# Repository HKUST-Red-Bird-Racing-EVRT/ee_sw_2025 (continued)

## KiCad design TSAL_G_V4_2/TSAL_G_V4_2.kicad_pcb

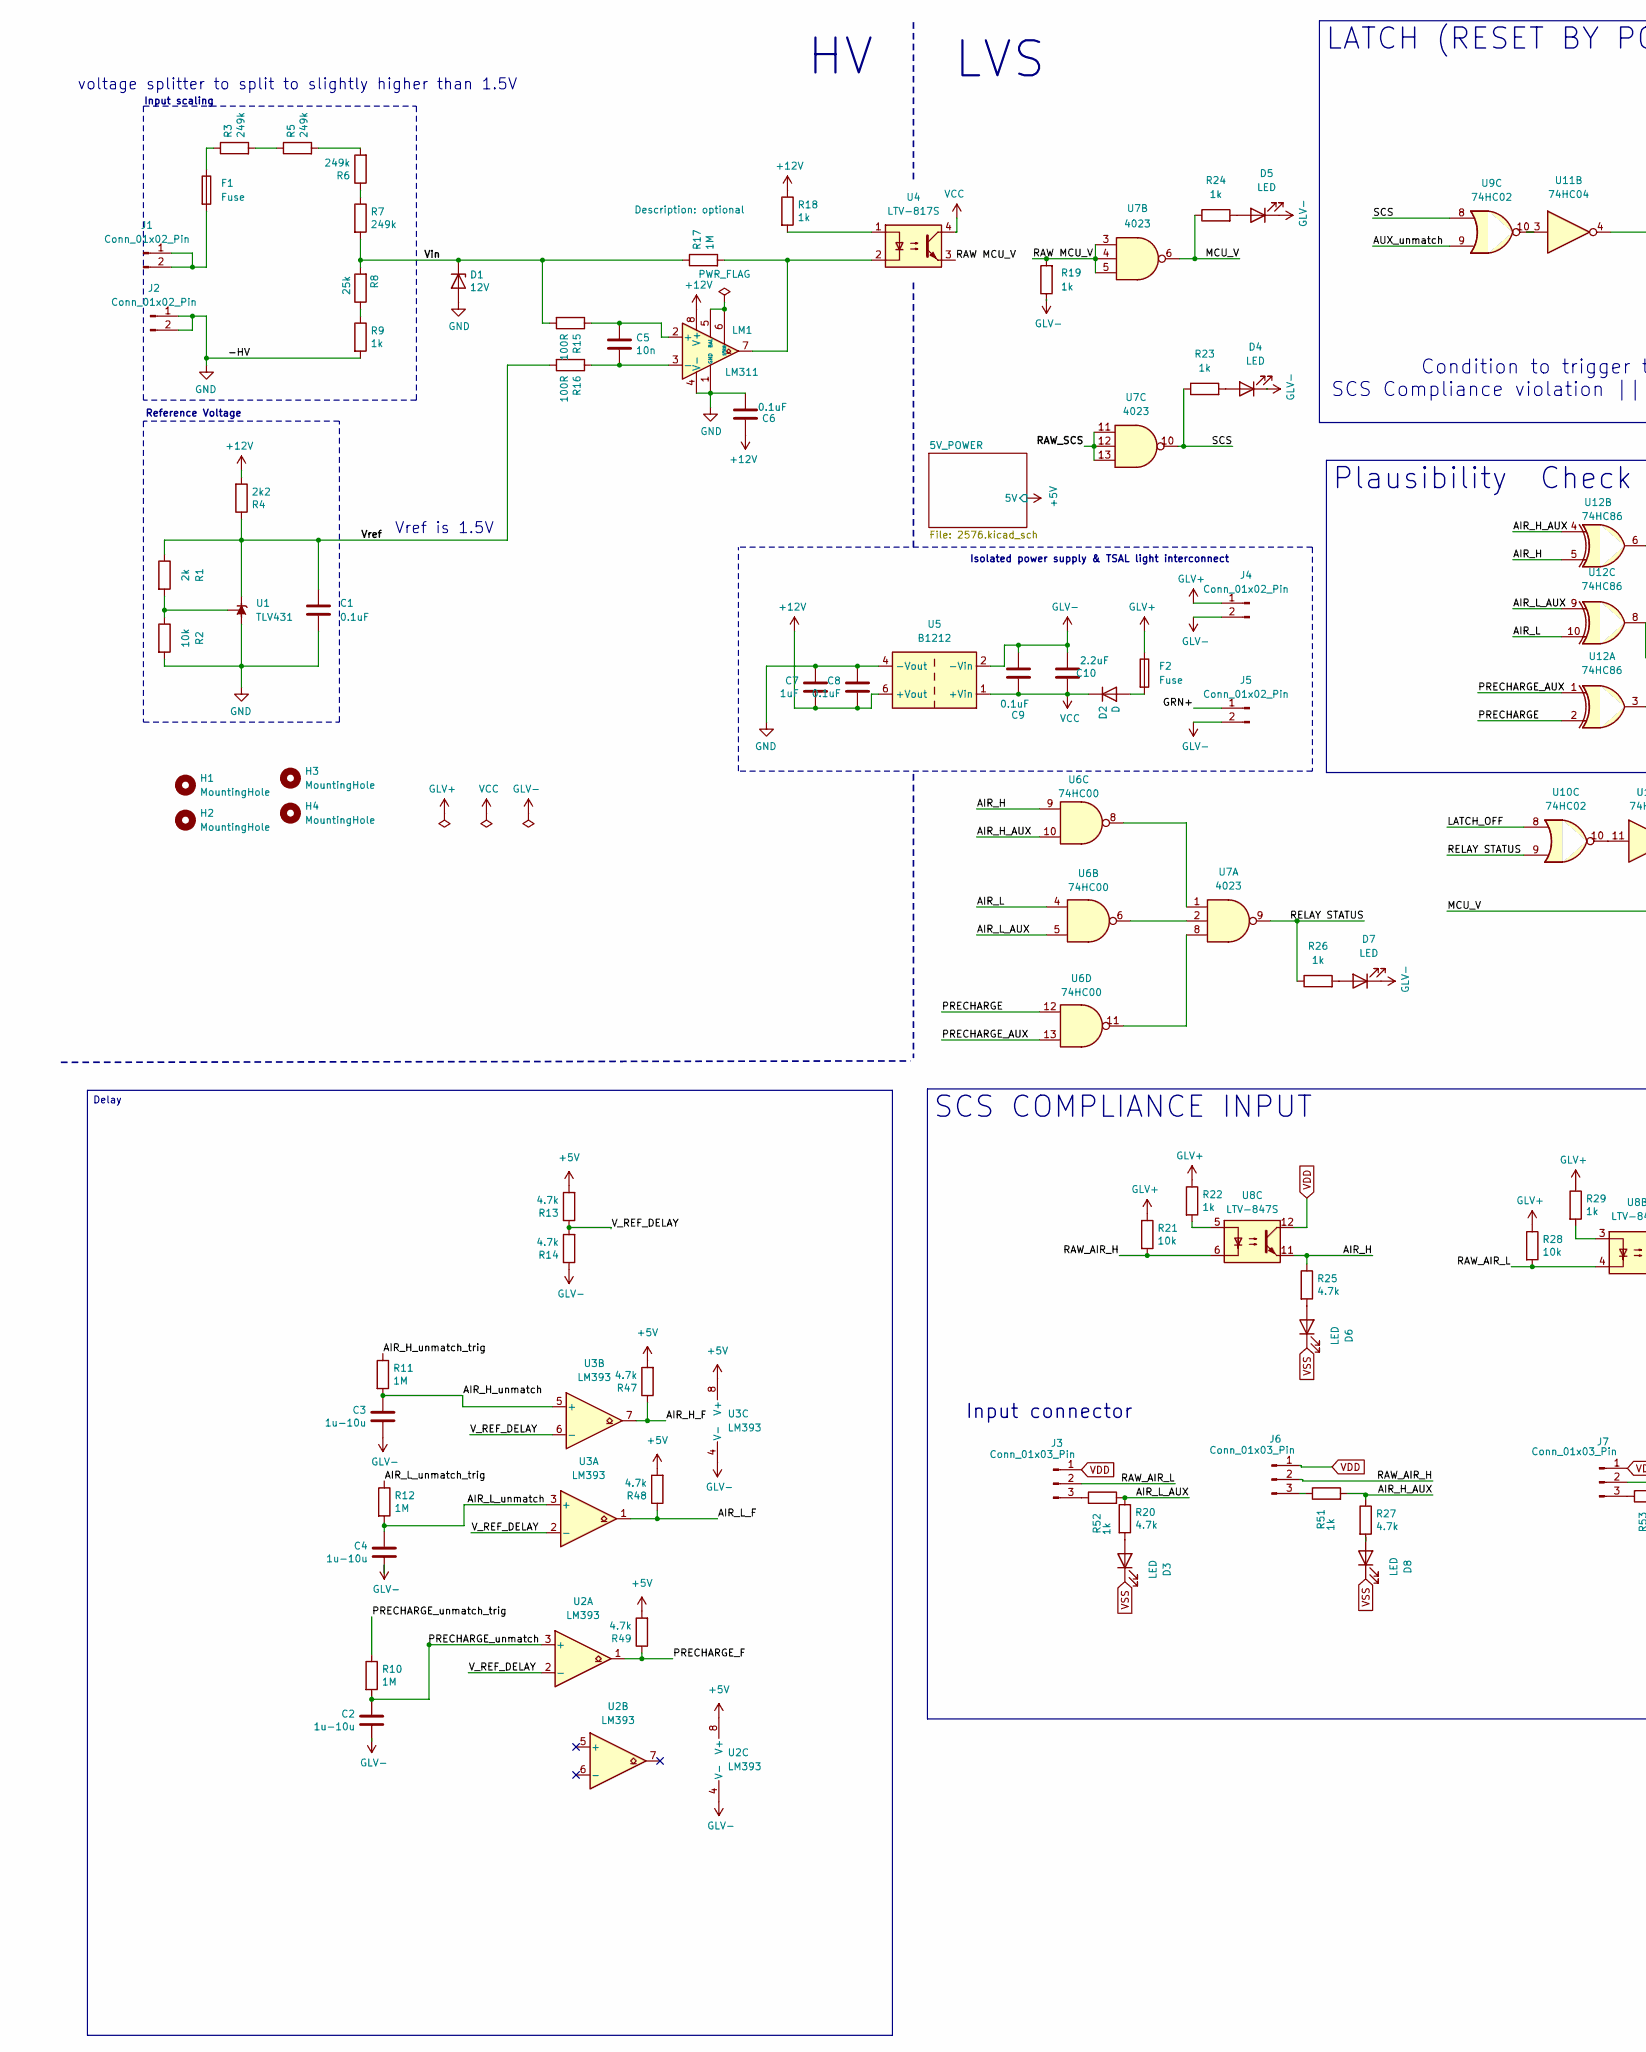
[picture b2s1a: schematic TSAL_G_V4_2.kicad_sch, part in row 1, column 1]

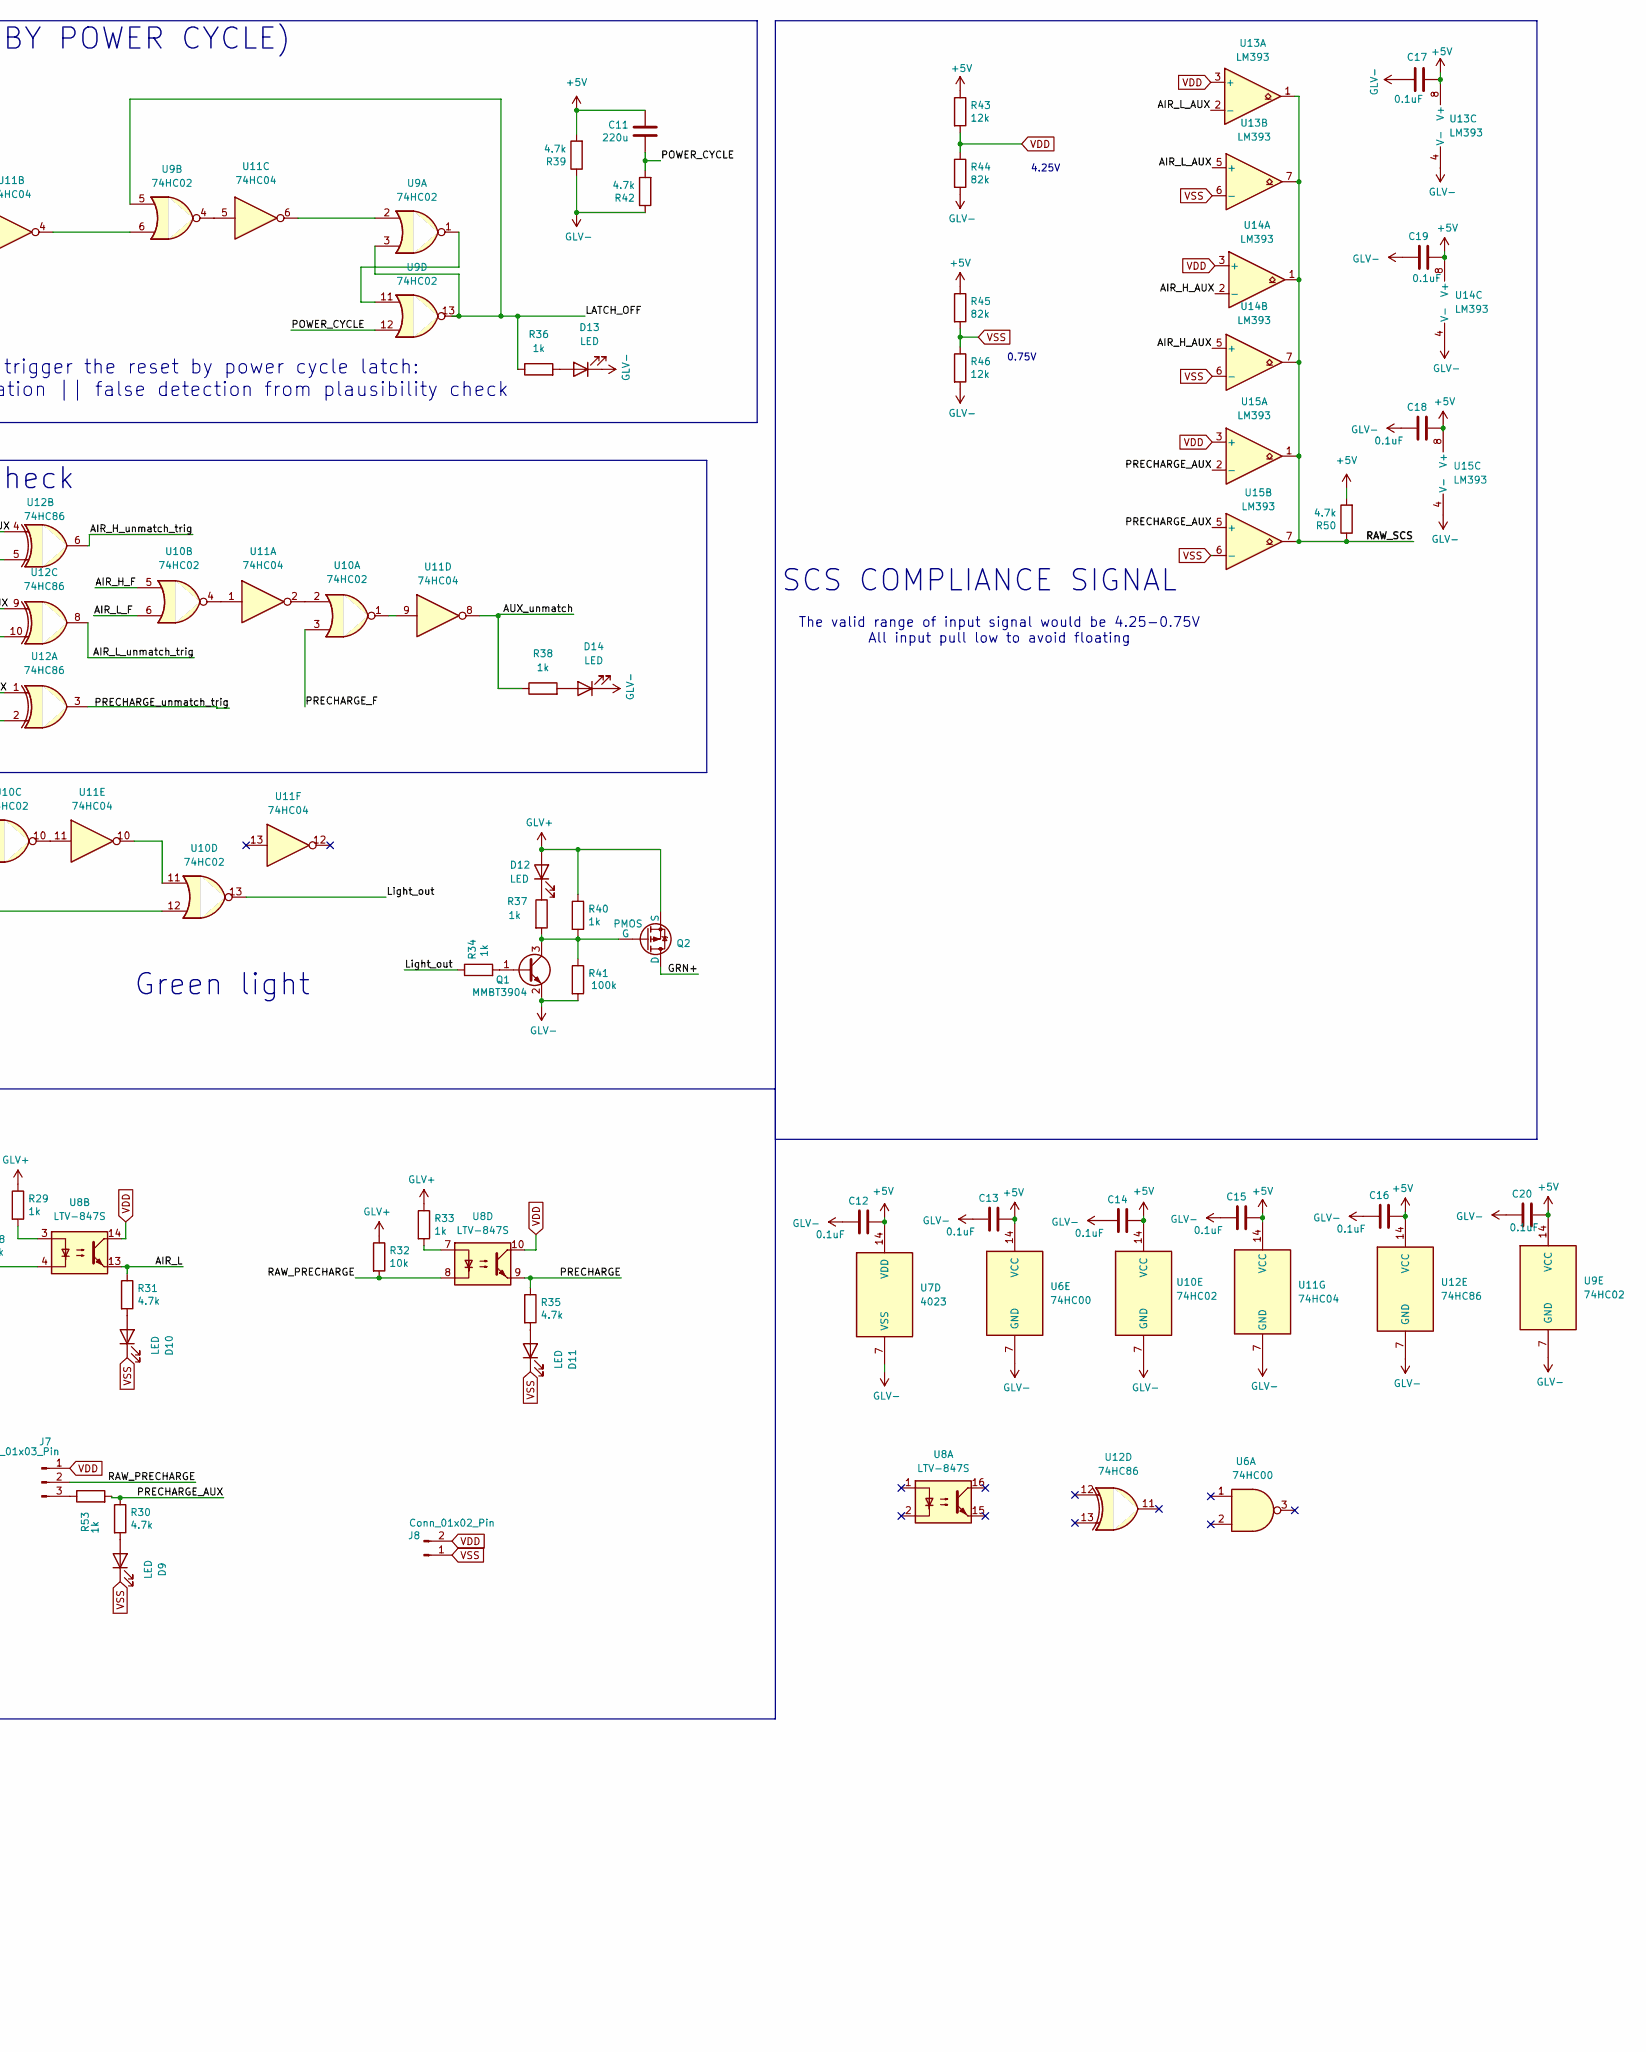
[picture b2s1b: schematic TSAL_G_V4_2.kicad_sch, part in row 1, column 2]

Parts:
C1, C6, C8, C9, C12, C13, C14, C15, C16, C17, C18, C19, C20: 0.1uF; C_0805_2012Metric_Pad1.18x1.45mm_HandSolder_L
C2, C3, C4: 1u-10u; C_0805_2012Metric_Pad1.18x1.45mm_HandSolder_L
C5: 10n; C_0805_2012Metric_Pad1.18x1.45mm_HandSolder_L
C7: 1uF; C_0805_2012Metric_Pad1.18x1.45mm_HandSolder_L
C10: 2.2uF; C_0805_2012Metric_Pad1.18x1.45mm_HandSolder_L
C11: 220u; CP_Radial_D5.0mm_P2.50mm
D1: 12V; D_DO-35_SOD27_P7.62mm_Horizontal
D2: D; D_SMA_Handsoldering
D3, D4, D5, D6, D7, D8, D9, D10, D11, D12, D13, D14: LED; LED_0805_2012Metric_Pad1.45x1.40mm_HandSolder
F1: Fuse; Fuse_Littelfuse-NANO2-885
F2: Fuse; Fuse_1210_3225Metric_Pad1.42x2.65mm_HandSolder
H1, H2, H3, H4: MountingHole; MountingHole_4.3mm_M4
J1, J2, J4, J5, J8: Conn_01x02_Pin; Molex_Micro-Fit_3.0_43650-0215_1x02_P3.00mm_Vertical
J3, J6, J7: Conn_01x03_Pin; Molex_Micro-Fit_3.0_43650-0315_1x03_P3.00mm_Vertical
LM1: LM311; SOIC-8_3.9x4.9mm_P1.27mm_RMC_Handsolder
Q1: MMBT3904; SOT-23
Q2: PMOS; TO-252-2
R1: 2k; R_0805_2012Metric_Pad1.20x1.40mm_HandSolder_L
R2, R21, R28, R32: 10k; R_0805_2012Metric_Pad1.20x1.40mm_HandSolder_L
R3, R5, R6, R7: 249k; R_0805_2012Metric_Pad1.20x1.40mm_HandSolder_L
R4: 2k2; R_0805_2012Metric_Pad1.20x1.40mm_HandSolder_L
R8: 25k; R_0805_2012Metric_Pad1.20x1.40mm_HandSolder_L
R9, R18, R19, R22, R23, R24, R26, R29, R33, R34, R36, R37, R38, R40, R51, R52, R53: 1k; R_0805_2012Metric_Pad1.20x1.40mm_HandSolder_L
R10, R11, R12, R17: 1M; R_0805_2012Metric_Pad1.20x1.40mm_HandSolder_L
R13, R14, R20, R25, R27, R30, R31, R35, R39, R42, R47, R48, R49, R50: 4.7k; R_0805_2012Metric_Pad1.20x1.40mm_HandSolder_L
R15, R16: 100R; R_0805_2012Metric_Pad1.20x1.40mm_HandSolder_L
R41: 100k; R_0805_2012Metric_Pad1.20x1.40mm_HandSolder_L
R43, R46: 12k; R_0805_2012Metric_Pad1.20x1.40mm_HandSolder_L
R44, R45: 82k; R_0805_2012Metric_Pad1.20x1.40mm_HandSolder_L
U1: TLV431; SOT-23
U2, U3, U13, U14, U15: LM393; SOIC-8_3.9x4.9mm_P1.27mm_RMC_Handsolder
U4: LTV-817S; SMDIP-4_W9.53mm
U5: B1212; Converter_DCDC_F1212
U6: 74HC00; SOIC127P600X175-14N
U7: 4023; SOIC127P600X175-14N
U8: LTV-847S; SMDIP-16_W9.53mm
U9, U10: 74HC02; SOIC127P600X175-14N
U11: 74HC04; SOIC127P600X175-14N
U12: 74HC86; SOIC127P600X175-14N

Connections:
+5V: C11.1, C12.2, C13.2, C14.2, C15.2, C16.2, C17.2, C18.2, C19.2, C20.2, R13.2, R39.2, R43.1, R45.1, R47.2, R48.2, R49.2, R50.2, U2.8 (V+), U3.8 (V+), U6.14 (VCC), U7.14 (VDD), U9.14 (VCC), U10.14 (VCC), U11.14 (VCC), U12.14 (VCC), U13.8 (V+), U14.8 (V+), U15.8 (V+); also elsewhere on the board
+12V: C6.1, C7.2, C8.2, LM1.8 (V+), R4.2, R18.1, U5.6 (+Vout)
/AIR_H: R25.1, U6.9, U8.11, U12.5
/AIR_H_AUX: R27.1, R51.2, U6.10, U12.4, U14.2 (-), U14.5 (+)
/AIR_H_F: R47.1, U3.7, U10.5
/AIR_H_unmatch: C3.1, R11.2, U3.5 (+)
/AIR_H_unmatch_trig: R11.1, U12.6
/AIR_L: R31.1, U6.4, U8.13, U12.10
/AIR_L_AUX: R20.1, R52.2, U6.5, U12.9, U13.2 (-), U13.5 (+)
/AIR_L_F: R48.1, U3.1, U10.6
/AIR_L_unmatch: C4.1, R12.2, U3.3 (+)
/AIR_L_unmatch_trig: R12.1, U12.8
/AUX_unmatch: R38.1, U9.9, U11.8
/GRN+: J5.1, Q2.1 (D)
/LATCH_OFF: R36.1, U9.3, U9.5, U9.13, U10.8
/Light_out: R34.1, U10.13
/MCU_V: R24.1, U7.6, U10.12
/POWER_CYCLE: C11.2, R42.2, U9.12
/PRECHARGE: R35.1, U6.12, U8.9, U12.2
/PRECHARGE_AUX: R30.1, R53.2, U6.13, U12.1, U15.2 (-), U15.5 (+)
/PRECHARGE_F: R49.1, U2.1, U10.3
/PRECHARGE_unmatch: C2.1, R10.2, U2.3 (+)
/PRECHARGE_unmatch_trig: R10.1, U12.3
/RAW MCU_V: R19.2, U4.3, U7.3, U7.4, U7.5
/RAW_AIR_H: J6.2, R21.2, U8.6
/RAW_AIR_L: J3.2, R28.2, U8.4
/RAW_PRECHARGE: J7.2, R32.2, U8.8
/RAW_SCS: R50.1, U7.11, U7.12, U7.13, U13.1, U13.7, U14.1, U14.7, U15.1, U15.7
/RELAY STATUS: R26.1, U7.9, U10.9
/SCS: R23.1, U7.10, U9.8
/V_REF_DELAY: R13.1, R14.2, U2.2 (-), U3.2 (-), U3.6 (-)
/Vin: D1.1 (K), R7.2, R8.2, R15.2, R17.1
/Vref: C1.1, R1.1, R4.1, R16.2, U1.2 (K)
GLV+: D12.2 (A), F2.1, J4.1, Q2.3 (S), R21.1, R22.1, R28.1, R29.1, R32.1, R33.1, R40.1
GLV-: C2.2, C3.2, C4.2, C9.1, C10.1, C12.1, C13.1, C14.1, C15.1, C16.1, C17.1, C18.1, C19.1, C20.1, D4.1 (K), D5.1 (K), D7.1 (K), D13.1 (K), D14.1 (K), J4.2, J5.2, Q1.2 (E), R14.1, R19.1, R39.1, R41.2, R42.1, R44.2, R46.2, U2.4 (V-), U3.4 (V-), U5.2 (-Vin), U6.7 (GND), U7.7 (VSS), U9.7 (GND), U10.7 (GND), U11.7 (GND), U12.7 (GND), U13.4 (V-), U14.4 (V-), U15.4 (V-); also elsewhere on the board
GND: C1.2, C6.2, C7.1, C8.1, D1.2 (A), J2.1, J2.2, LM1.1 (GND), LM1.4 (V-), R2.2, R9.2, U1.3 (A), U5.4 (-Vout)
unnamed: D2.2 (A), F2.2
unnamed: D3.2 (A), R20.2
unnamed: D4.2 (A), R23.2
unnamed: D5.2 (A), R24.2
unnamed: D6.2 (A), R25.2
unnamed: D7.2 (A), R26.2
unnamed: D8.2 (A), R27.2
unnamed: D9.2 (A), R30.2
unnamed: D10.2 (A), R31.2
unnamed: D11.2 (A), R35.2
unnamed: D12.1 (K), R37.1
unnamed: D13.2 (A), R36.2
unnamed: D14.2 (A), R38.2
unnamed: F1.1, R3.1
unnamed: F1.2, J1.1, J1.2
unnamed: J3.3, R52.1
unnamed: J6.3, R51.1
unnamed: J7.3, R53.1
unnamed: C5.1, LM1.2 (+), R15.1
unnamed: C5.2, LM1.3 (-), R16.1
unnamed: LM1.5 (BAL), LM1.6 (STRB)
unnamed: LM1.7, R17.2, U4.2
unnamed: Q1.1 (B), R34.2
unnamed: Q1.3 (C), Q2.2 (G), R37.2, R40.2, R41.1
unnamed: R3.2, R5.1
unnamed: R5.2, R6.2
unnamed: R6.1, R7.1
unnamed: R8.1, R9.1
unnamed: R18.2, U4.1
unnamed: R22.2, U8.5
unnamed: R29.2, U8.3
unnamed: R33.2, U8.7
unnamed: R1.2, R2.1, U1.1 (REF)
unnamed: U6.6, U7.2
unnamed: U6.8, U7.1
unnamed: U6.11, U7.8
unnamed: U9.1, U9.11
unnamed: U10.1, U11.9
unnamed: U10.2, U11.2
unnamed: U10.4, U11.1
unnamed: U10.10, U11.11
unnamed: U10.11, U11.10
unnamed: U9.10, U11.3
unnamed: U9.6, U11.4
unnamed: U9.4, U11.5
unnamed: U9.2, U11.6
VCC: C9.2, C10.2, D2.1 (K), U4.4, U5.1 (+Vin); also elsewhere on the board
VDD: J3.1, J6.1, J7.1, J8.2, R43.2, R44.1, U8.10, U8.12, U8.14, U13.3 (+), U14.3 (+), U15.3 (+)
VSS: D3.1 (K), D6.1 (K), D8.1 (K), D9.1 (K), D10.1 (K), D11.1 (K), J8.1, R45.2, R46.1, U13.6 (-), U14.6 (-), U15.6 (-)

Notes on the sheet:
0.75V
The valid range of input signal would be 4.25-0.75V All input pull low to avoid floating
LVS
Condition to trigger the reset by power cycle latch: SCS Compliance violation || false detection from plausibility check
Reference Voltage
voltage splitter to split to slightly higher than 1.5V
Vref is 1.5V
Green light
Isolated power supply & TSAL light interconnect
Input scaling
4.25V
Input connector
Plausibility Check
SCS COMPLIANCE SIGNAL
Delay
LATCH (RESET BY POWER CYCLE)
SCS COMPLIANCE INPUT

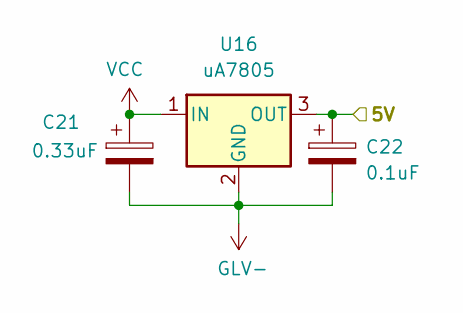
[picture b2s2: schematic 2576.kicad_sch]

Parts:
C21: 0.33uF; CP_Radial_D5.0mm_P2.50mm
C22: 0.1uF; CP_Radial_D5.0mm_P2.50mm
U16: uA7805; TO-252-2

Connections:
+5V: C22.1, U16.3 (OUT); also elsewhere on the board
GLV-: C21.2, C22.2, U16.2 (GND); also elsewhere on the board
VCC: C21.1, U16.1 (IN); also elsewhere on the board

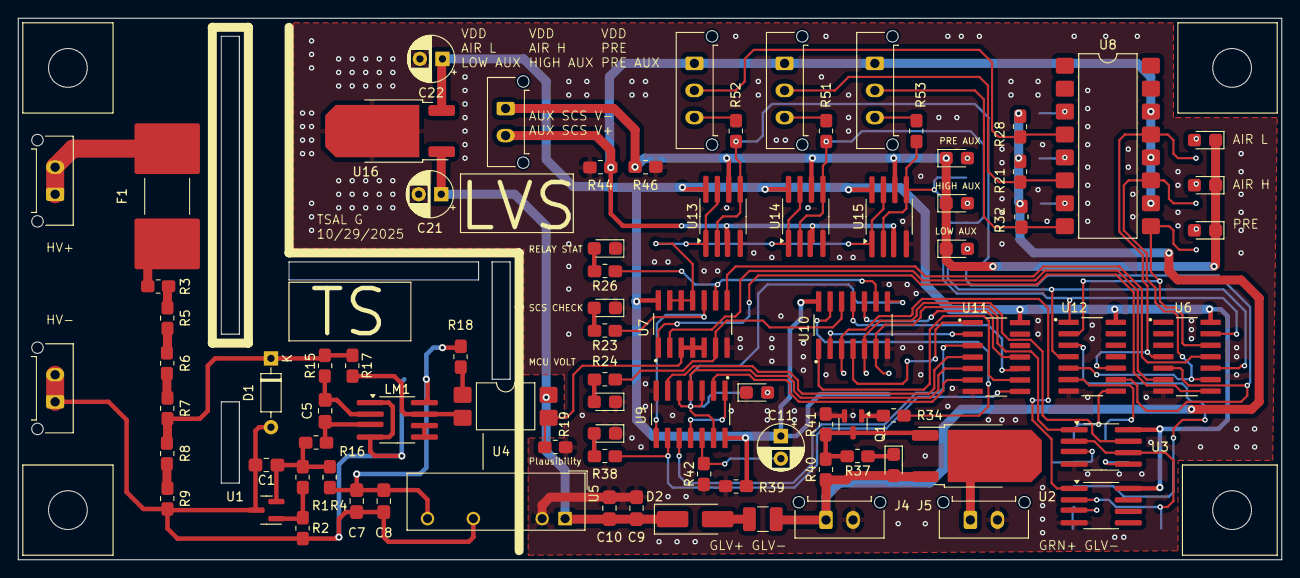
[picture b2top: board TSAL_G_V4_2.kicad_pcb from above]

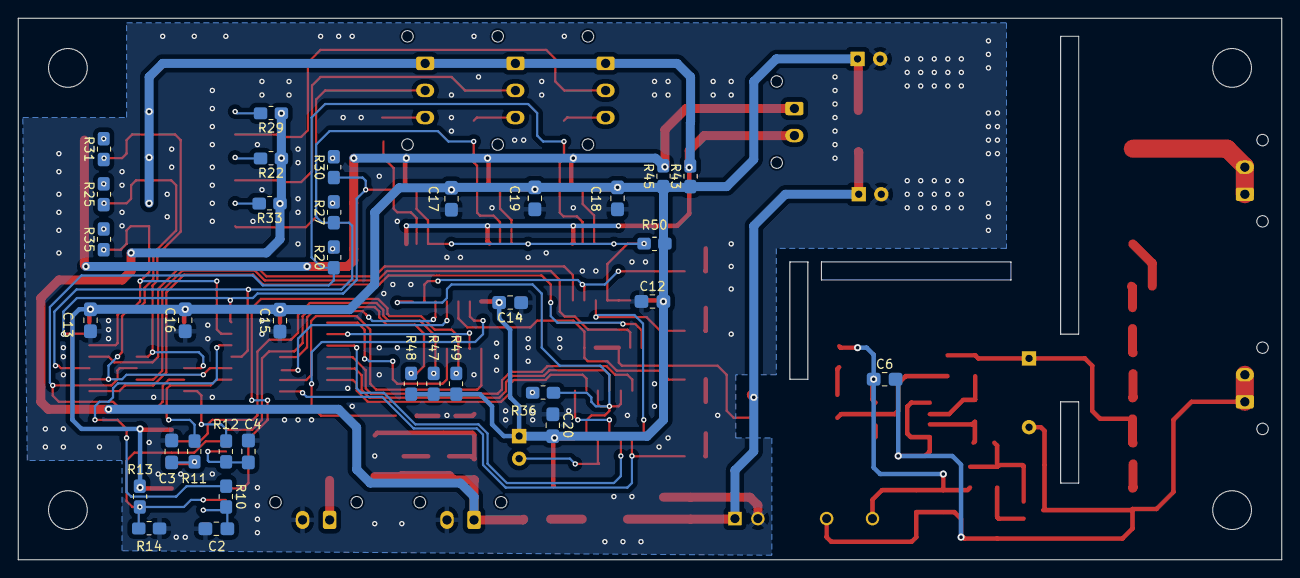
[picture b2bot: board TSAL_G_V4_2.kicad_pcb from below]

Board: 2 copper layers, 140.0 x 60.0 mm, 122 parts (34 on the bottom side), 85 nets.

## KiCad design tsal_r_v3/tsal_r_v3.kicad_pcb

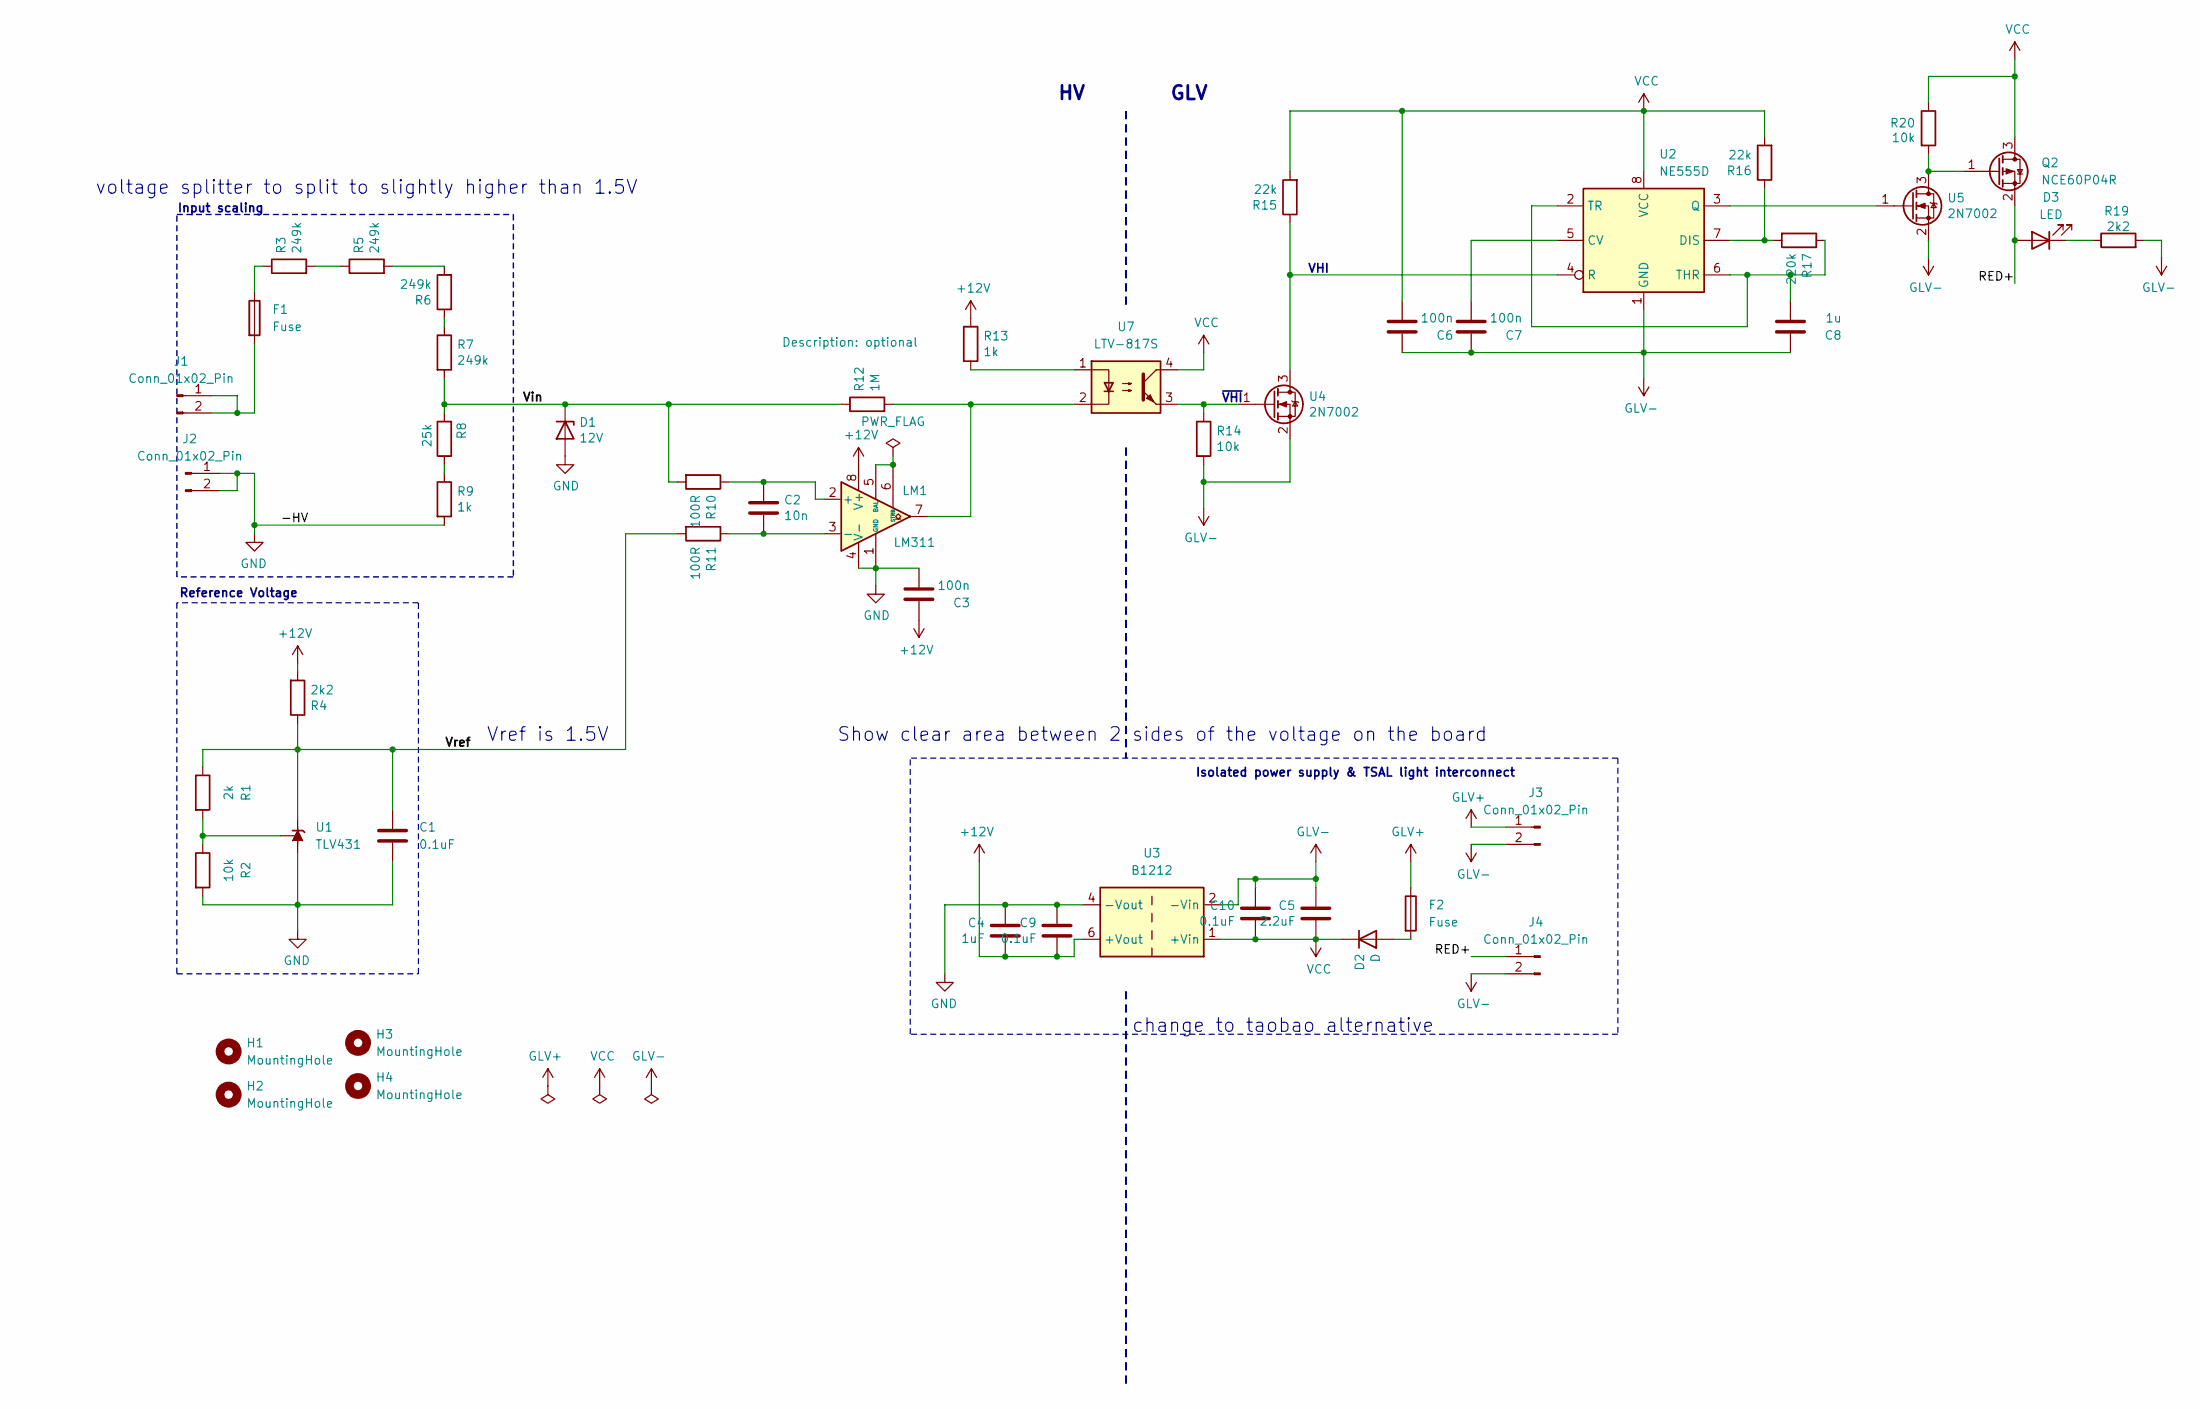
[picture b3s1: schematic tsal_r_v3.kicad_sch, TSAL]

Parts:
C1, C9, C10: 0.1uF; C_0805_2012Metric_Pad1.18x1.45mm_HandSolder_L
C2: 10n; C_0805_2012Metric_Pad1.18x1.45mm_HandSolder_L
C3, C6, C7: 100n; C_0805_2012Metric_Pad1.18x1.45mm_HandSolder_L
C4: 1uF; C_0805_2012Metric_Pad1.18x1.45mm_HandSolder_L
C5: 2.2uF; C_0805_2012Metric_Pad1.18x1.45mm_HandSolder_L
C8: 1u; C_0805_2012Metric_Pad1.18x1.45mm_HandSolder_L
D1: 12V; D_DO-35_SOD27_P7.62mm_Horizontal
D2: D; D_SMA_Handsoldering
D3: LED; LED_0805_2012Metric_Pad1.45x1.40mm_HandSolder
F1: Fuse; Fuse_Littelfuse-NANO2-885
F2: Fuse; Fuse_1210_3225Metric_Pad1.42x2.65mm_HandSolder
H1, H2, H3, H4: MountingHole; MountingHole_3.2mm_M3
J1, J2, J3, J4: Conn_01x02_Pin; Molex_Micro-Fit_3.0_43650-0200_1x02_P3.00mm_Horizontal
LM1: LM311; SOIC-8_3.9x4.9mm_P1.27mm_RMC_Handsolder
Q2: NCE60P04R; TO-252-2
R1: 2k; R_0805_2012Metric_Pad1.20x1.40mm_HandSolder_L
R2, R14, R20: 10k; R_0805_2012Metric_Pad1.20x1.40mm_HandSolder_L
R3, R5, R6, R7: 249k; R_0805_2012Metric_Pad1.20x1.40mm_HandSolder_L
R4, R19: 2k2; R_0805_2012Metric_Pad1.20x1.40mm_HandSolder_L
R8: 25k; R_0805_2012Metric_Pad1.20x1.40mm_HandSolder_L
R9, R13: 1k; R_0805_2012Metric_Pad1.20x1.40mm_HandSolder_L
R10, R11: 100R; R_0805_2012Metric_Pad1.20x1.40mm_HandSolder_L
R12: 1M; R_0805_2012Metric_Pad1.20x1.40mm_HandSolder_L
R15, R16: 22k; R_0805_2012Metric_Pad1.20x1.40mm_HandSolder_L
R17: 220k; R_0805_2012Metric_Pad1.20x1.40mm_HandSolder_L
U1: TLV431; SOT-23
U2: NE555D; SOIC-8_3.9x4.9mm_P1.27mm_RMC_Handsolder
U3: B1212; DCDC Converter F1212
U4, U5: 2N7002; SOT-23
U7: LTV-817S; SMDIP-4_W9.53mm

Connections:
+12V: C3.1, C4.2, C9.2, LM1.8 (V+), R4.2, R13.1, U3.6 (+Vout)
/RED+: D3.2 (A), J4.1, Q2.2 (S)
/Vin: D1.1 (K), R7.2, R8.2, R10.2, R12.1
/Vref: C1.1, R1.1, R4.1, R11.2, U1.2 (K)
GLV+: F2.1, J3.1
GLV-: C5.1, C6.1, C7.1, C8.1, C10.1, J3.2, J4.2, R14.2, R19.2, U2.1 (GND), U3.2 (-Vin), U4.2 (S), U5.2 (S)
GND: C1.2, C3.2, C4.1, C9.1, D1.2 (A), J2.1, J2.2, LM1.1 (GND), LM1.4 (V-), R2.2, R9.2, U1.3 (A), U3.4 (-Vout)
unnamed: D2.2 (A), F2.2
unnamed: D3.1 (K), R19.1
unnamed: F1.1, R3.1
unnamed: F1.2, J1.1, J1.2
unnamed: C2.1, LM1.2 (+), R10.1
unnamed: C2.2, LM1.3 (-), R11.1
unnamed: LM1.5 (BAL), LM1.6 (STRB)
unnamed: LM1.7, R12.2, U7.2
unnamed: Q2.1 (G), R20.2, U5.3 (D)
unnamed: R3.2, R5.1
unnamed: R5.2, R6.2
unnamed: R6.1, R7.1
unnamed: R8.1, R9.1
unnamed: R13.2, U7.1
unnamed: R1.2, R2.1, U1.1 (REF)
unnamed: C7.2, U2.5 (CV)
unnamed: R16.1, R17.2, U2.7 (DIS)
unnamed: U2.3 (Q), U5.1 (G)
unnamed: R15.1, U2.4 (R), U4.3 (D)
unnamed: C8.2, R17.1, U2.2 (TR), U2.6 (THR)
unnamed: R14.1, U4.1 (G), U7.3
VCC: C5.2, C6.2, C10.2, D2.1 (K), Q2.3 (D), R15.2, R16.2, R20.1, U2.8 (VCC), U3.1 (+Vin), U7.4

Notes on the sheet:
change to taobao alternative
voltage splitter to split to slightly higher than 1.5V
Show clear area between 2 sides of the voltage on the board
Isolated power supply & TSAL light interconnect
Reference Voltage
~{VHI}
Input scaling
GLV
VHI
Vref is 1.5V

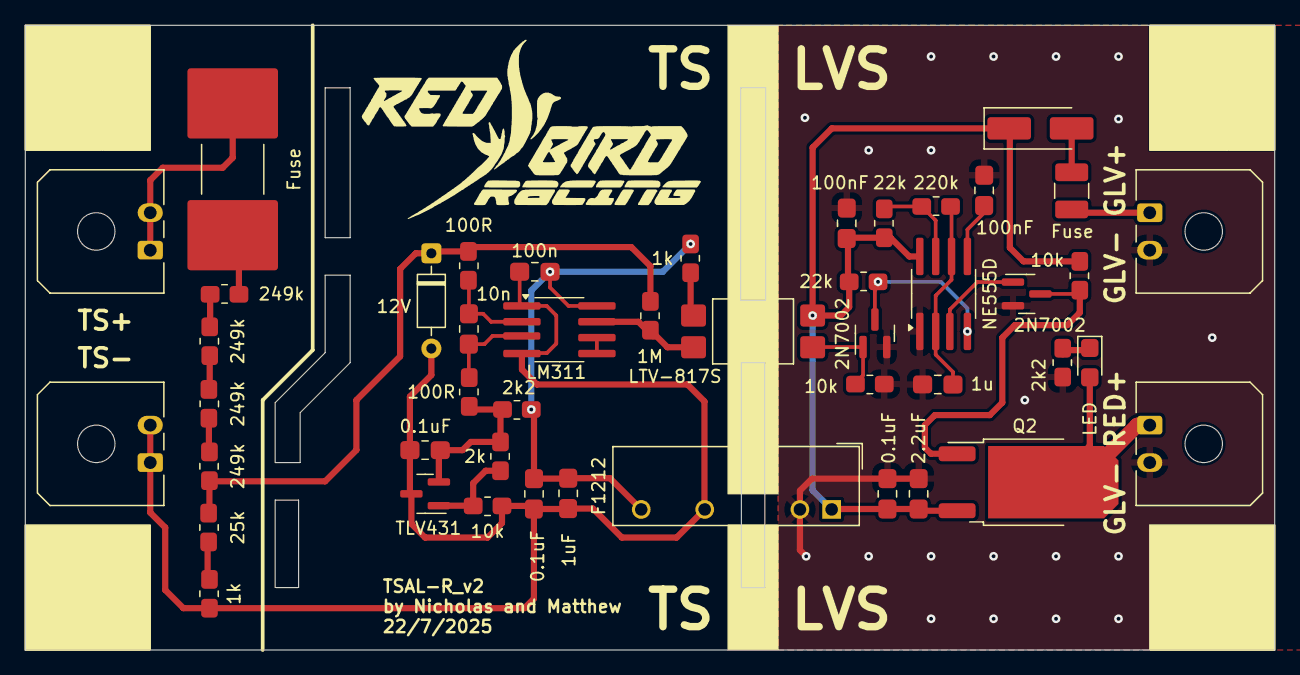
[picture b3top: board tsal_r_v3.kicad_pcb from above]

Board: 2 copper layers, 100.0 x 50.0 mm, 50 parts (0 on the bottom side), 29 nets.
